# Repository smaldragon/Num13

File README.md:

# Num13

**Num13** is a 45-key compact ortholinear mechanical keyboard which includes a **Num**pad and is **13**Ux4U in size, which I designed for my own personal use.

The build is composed of 2 PCBs, the **top** pcb includes the key matrix (MX switches or low-profile Redragon switches w/ plate stabs), while the **bottom** includes the keyboard controller (a pi pico), a status led (rgb on the rB revision included here), and serves as the base of the keyboard structure itself.

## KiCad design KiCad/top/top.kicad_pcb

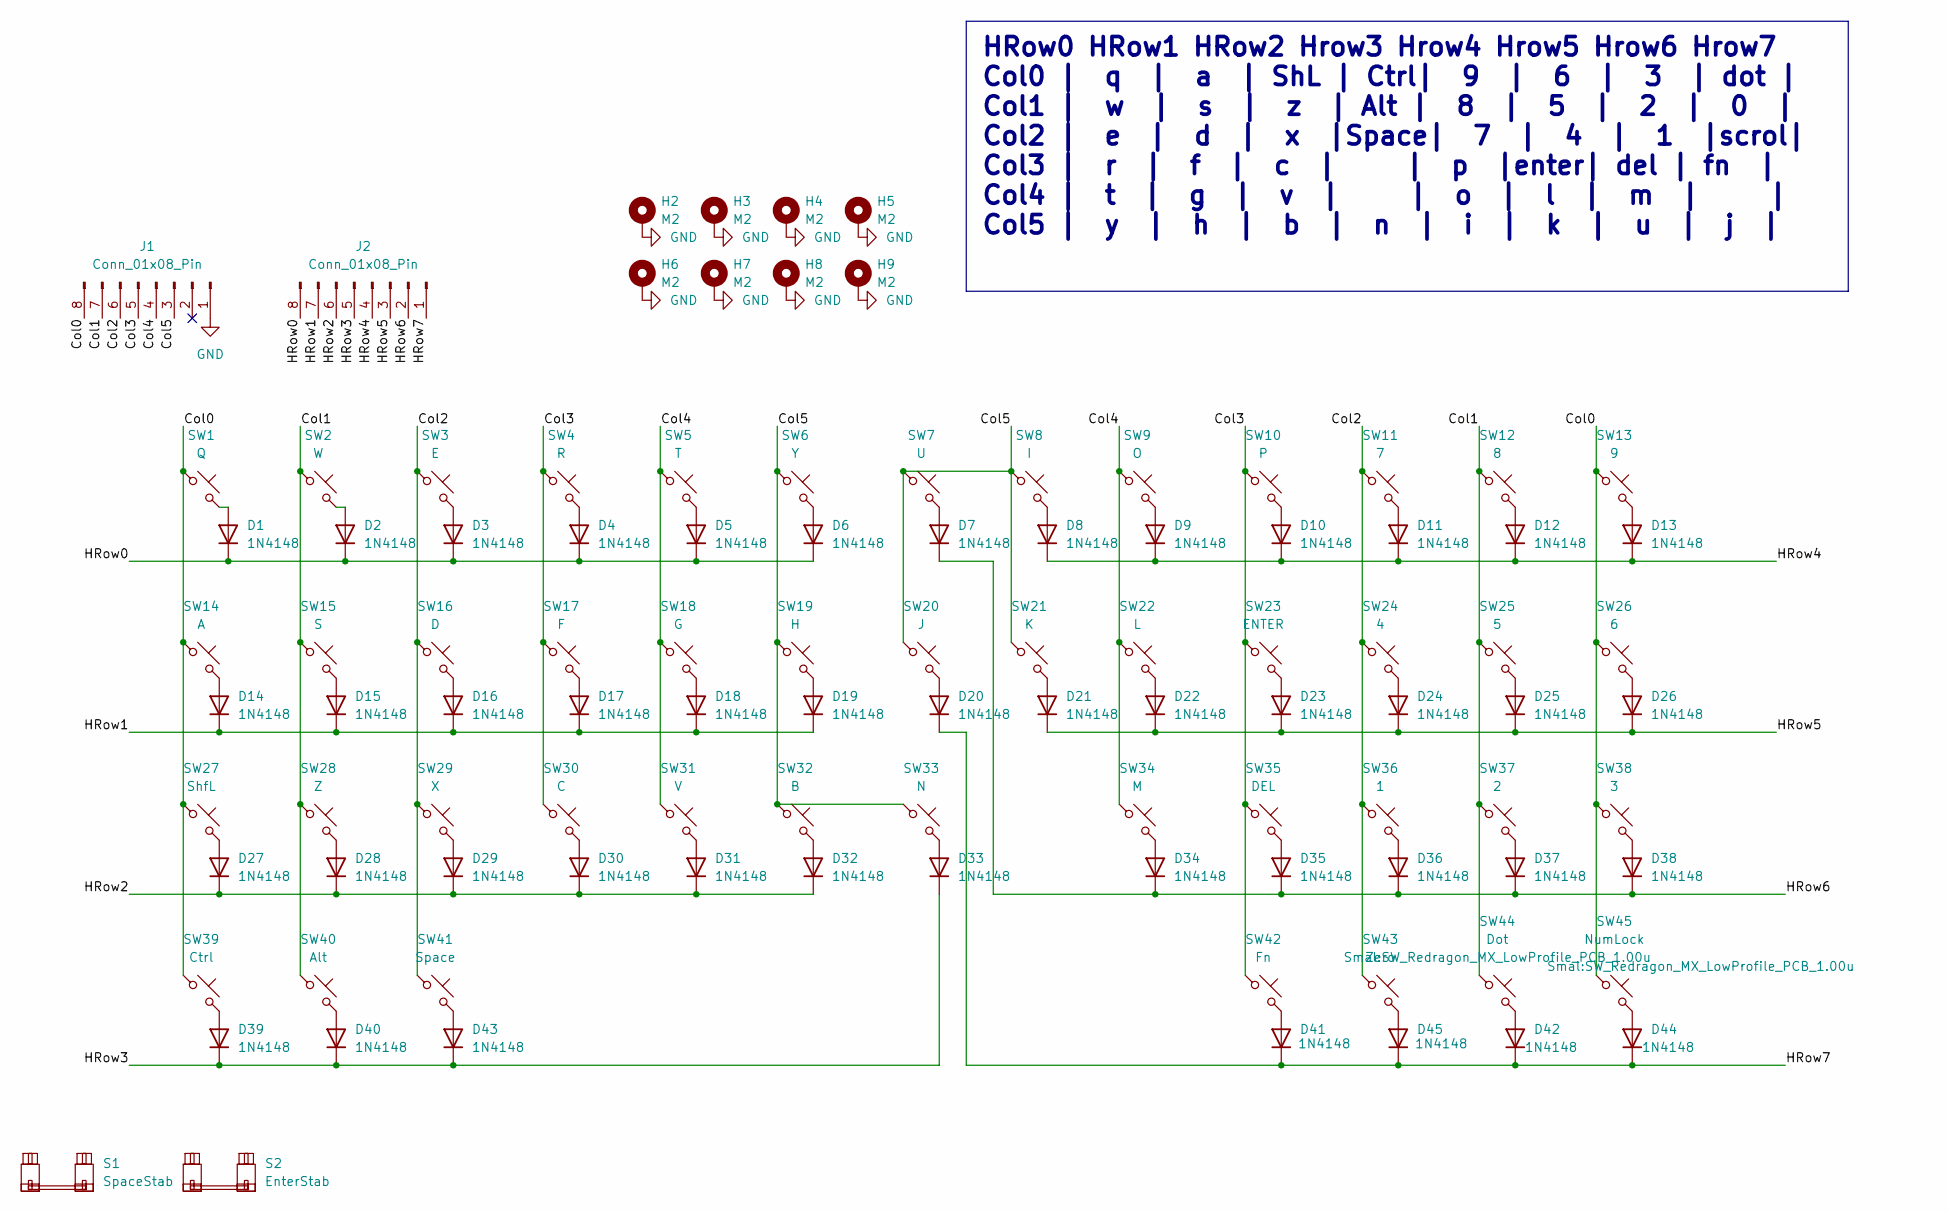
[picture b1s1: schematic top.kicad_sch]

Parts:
D1, D2, D3, D4, D5, D6, D7, D8, D9, D10, D11, D12, D13, D14, D15, D16, D17, D18, D19, D20, D21, D22, D23, D24, D25, D26, D27, D28, D29, D30, D31, D32, D33, D34, D35, D36, D37, D38, D39, D40, D41, D42, D43, D44, D45: 1N4148; D_DO-35_SOD27_P7.62mm_Horizontal
H2, H3, H4, H5, H6, H7, H8, H9: M2; MountingHole_2.2mm_M2_Pad
J1, J2: Conn_01x08_Pin; PinHeader_1x08_P2.54mm_Vertical
S1: SpaceStab; ks27_7u_pcb_cherry_plate
S2: EnterStab; ks27_2u_pcb_cherry_plate_stab
SW1: Q; SW_Redragon_MX_LowProfile_PCB_1.00u
SW2: W; SW_Redragon_MX_LowProfile_PCB_1.00u
SW3: E; SW_Redragon_MX_LowProfile_PCB_1.00u
SW4: R; SW_Redragon_MX_LowProfile_PCB_1.00u
SW5: T; SW_Redragon_MX_LowProfile_PCB_1.00u
SW6: Y; SW_Redragon_MX_LowProfile_PCB_1.00u
SW7: U; SW_Redragon_MX_LowProfile_PCB_1.00u
SW8: I; SW_Redragon_MX_LowProfile_PCB_1.00u
SW9: O; SW_Redragon_MX_LowProfile_PCB_1.00u
SW10: P; SW_Redragon_MX_LowProfile_PCB_1.00u
SW11: 7; SW_Redragon_MX_LowProfile_PCB_1.00u
SW12: 8; SW_Redragon_MX_LowProfile_PCB_1.00u
SW13: 9; SW_Redragon_MX_LowProfile_PCB_1.00u
SW14: A; SW_Redragon_MX_LowProfile_PCB_1.00u
SW15: S; SW_Redragon_MX_LowProfile_PCB_1.00u
SW16: D; SW_Redragon_MX_LowProfile_PCB_1.00u
SW17: F; SW_Redragon_MX_LowProfile_PCB_1.00u
SW18: G; SW_Redragon_MX_LowProfile_PCB_1.00u
SW19: H; SW_Redragon_MX_LowProfile_PCB_1.00u
SW20: J; SW_Redragon_MX_LowProfile_PCB_1.00u
SW21: K; SW_Redragon_MX_LowProfile_PCB_1.00u
SW22: L; SW_Redragon_MX_LowProfile_PCB_1.00u
SW23: ENTER; SW_Redragon_MX_LowProfile_PCB_2.00u
SW24: 4; SW_Redragon_MX_LowProfile_PCB_1.00u
SW25: 5; SW_Redragon_MX_LowProfile_PCB_1.00u
SW26: 6; SW_Redragon_MX_LowProfile_PCB_1.00u
SW27: ShfL; SW_Redragon_MX_LowProfile_PCB_1.00u
SW28: Z; SW_Redragon_MX_LowProfile_PCB_1.00u
SW29: X; SW_Redragon_MX_LowProfile_PCB_1.00u
SW30: C; SW_Redragon_MX_LowProfile_PCB_1.00u
SW31: V; SW_Redragon_MX_LowProfile_PCB_1.00u
SW32: B; SW_Redragon_MX_LowProfile_PCB_1.00u
SW33: N; SW_Redragon_MX_LowProfile_PCB_1.00u
SW34: M; SW_Redragon_MX_LowProfile_PCB_1.00u
SW35: DEL; SW_Redragon_MX_LowProfile_PCB_1.00u
SW36: 1; SW_Redragon_MX_LowProfile_PCB_1.00u
SW37: 2; SW_Redragon_MX_LowProfile_PCB_1.00u
SW38: 3; SW_Redragon_MX_LowProfile_PCB_1.00u
SW39: Ctrl; SW_Redragon_MX_LowProfile_PCB_1.00u
SW40: Alt; SW_Redragon_MX_LowProfile_PCB_1.00u
SW41: Space; SW_Redragon_MX_LowProfile_PCB_7.00u
SW42: Fn; SW_Redragon_MX_LowProfile_PCB_1.00u
SW43: Zero; SW_Redragon_MX_LowProfile_PCB_1.00u
SW44: Dot; SW_Redragon_MX_LowProfile_PCB_1.00u
SW45: NumLock; SW_Redragon_MX_LowProfile_PCB_1.00u

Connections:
/Col0: J1.8, SW1.1, SW13.1, SW14.1, SW26.1, SW27.1, SW38.1, SW39.1, SW45.1
/Col1: J1.7, SW2.1, SW12.1, SW15.1, SW25.1, SW28.1, SW37.1, SW40.1, SW44.1
/Col2: J1.6, SW3.1, SW11.1, SW16.1, SW24.1, SW29.1, SW36.1, SW41.1, SW43.1
/Col3: J1.5, SW4.1, SW10.1, SW17.1, SW23.1, SW30.1, SW35.1, SW42.1
/Col4: J1.4, SW5.1, SW9.1, SW18.1, SW22.1, SW31.1, SW34.1
/Col5: J1.3, SW6.1, SW7.1, SW8.1, SW19.1, SW20.1, SW21.1, SW32.1, SW33.1
/HRow0: D1.1 (K), D2.1 (K), D3.1 (K), D4.1 (K), D5.1 (K), D6.1 (K), J2.8
/HRow1: D14.1 (K), D15.1 (K), D16.1 (K), D17.1 (K), D18.1 (K), D19.1 (K), J2.7
/HRow2: D27.1 (K), D28.1 (K), D29.1 (K), D30.1 (K), D31.1 (K), D32.1 (K), J2.6
/HRow3: D33.1 (K), D39.1 (K), D40.1 (K), D43.1 (K), J2.5
/HRow4: D8.1 (K), D9.1 (K), D10.1 (K), D11.1 (K), D12.1 (K), D13.1 (K), J2.4
/HRow5: D21.1 (K), D22.1 (K), D23.1 (K), D24.1 (K), D25.1 (K), D26.1 (K), J2.3
/HRow6: D7.1 (K), D34.1 (K), D35.1 (K), D36.1 (K), D37.1 (K), D38.1 (K), J2.2
/HRow7: D20.1 (K), D41.1 (K), D42.1 (K), D44.1 (K), D45.1 (K), J2.1
GND: H2.1, H3.1, H4.1, H5.1, H6.1, H7.1, H8.1, H9.1, J1.1
unnamed: D1.2 (A), SW1.2
unnamed: D2.2 (A), SW2.2
unnamed: D3.2 (A), SW3.2
unnamed: D4.2 (A), SW4.2
unnamed: D5.2 (A), SW5.2
unnamed: D6.2 (A), SW6.2
unnamed: D7.2 (A), SW7.2
unnamed: D8.2 (A), SW8.2
unnamed: D9.2 (A), SW9.2
unnamed: D10.2 (A), SW10.2
unnamed: D11.2 (A), SW11.2
unnamed: D12.2 (A), SW12.2
unnamed: D13.2 (A), SW13.2
unnamed: D14.2 (A), SW14.2
unnamed: D15.2 (A), SW15.2
unnamed: D16.2 (A), SW16.2
unnamed: D17.2 (A), SW17.2
unnamed: D18.2 (A), SW18.2
unnamed: D19.2 (A), SW19.2
unnamed: D20.2 (A), SW20.2
unnamed: D21.2 (A), SW21.2
unnamed: D22.2 (A), SW22.2
unnamed: D23.2 (A), SW23.2
unnamed: D24.2 (A), SW24.2
unnamed: D25.2 (A), SW25.2
unnamed: D26.2 (A), SW26.2
unnamed: D27.2 (A), SW27.2
unnamed: D28.2 (A), SW28.2
unnamed: D29.2 (A), SW29.2
unnamed: D30.2 (A), SW30.2
unnamed: D31.2 (A), SW31.2
unnamed: D32.2 (A), SW32.2
unnamed: D33.2 (A), SW33.2
unnamed: D34.2 (A), SW34.2
unnamed: D35.2 (A), SW35.2
unnamed: D36.2 (A), SW36.2
unnamed: D37.2 (A), SW37.2
unnamed: D38.2 (A), SW38.2
unnamed: D39.2 (A), SW39.2
unnamed: D40.2 (A), SW40.2
unnamed: D41.2 (A), SW42.2
unnamed: D42.2 (A), SW44.2
unnamed: D43.2 (A), SW41.2
unnamed: D44.2 (A), SW45.2
unnamed: D45.2 (A), SW43.2

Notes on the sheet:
HRow0 HRow1 HRow2 Hrow3 Hrow4 Hrow5 Hrow6 Hrow7 Col0 | q | a | ShL | Ctrl| 9 | 6 | 3 | dot | Col1 | w | s | z | Alt | 8 | 5 | 2 | 0 | Col2 | e | d | x |Space| 7 | 4 | 1 |scrol| Col3 | r | f | c | | p |enter| del | fn | Col4 | t | g | v | | o | l | m | | Col5 | y | h | b | n | i | k | u | j |

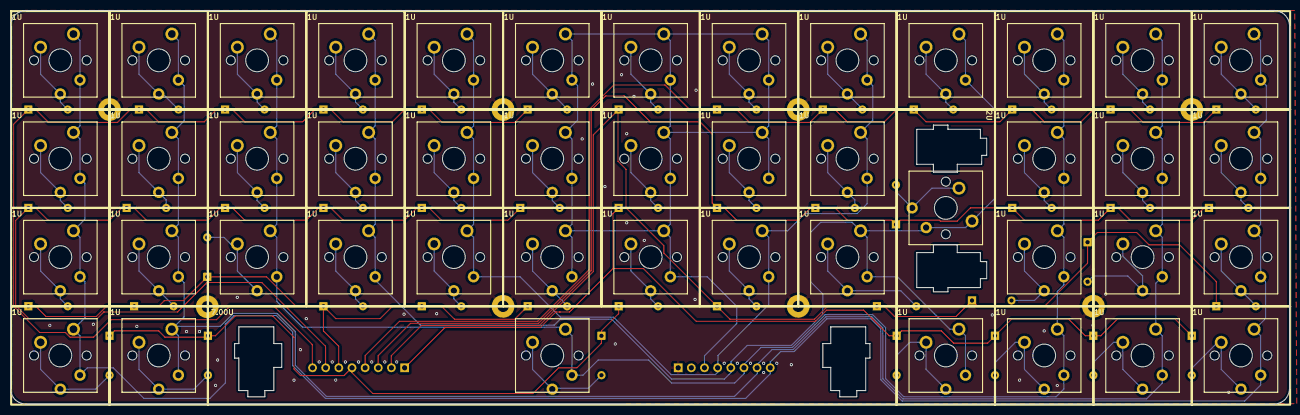
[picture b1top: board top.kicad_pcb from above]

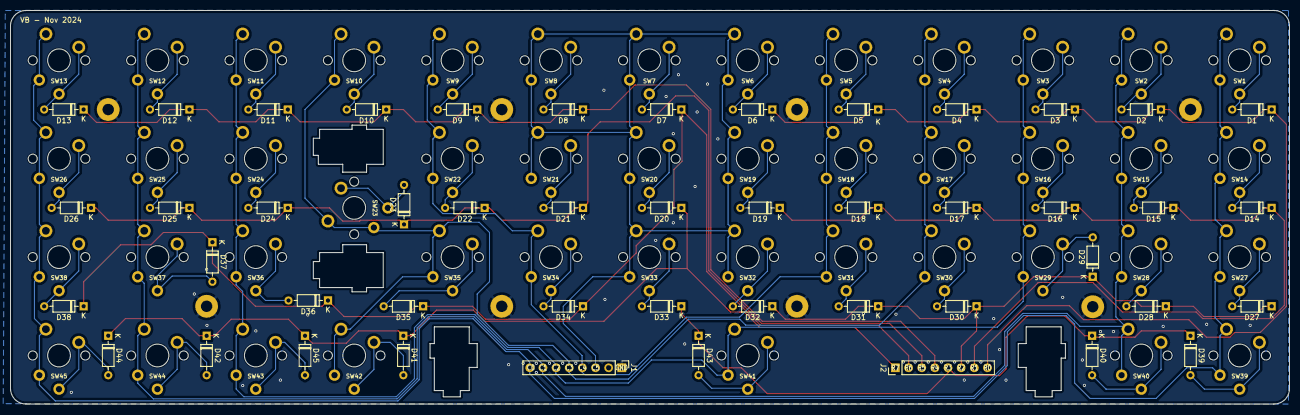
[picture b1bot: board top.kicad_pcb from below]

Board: 2 copper layers, 247.0 x 76.0 mm, 102 parts (47 on the bottom side), 60 nets.

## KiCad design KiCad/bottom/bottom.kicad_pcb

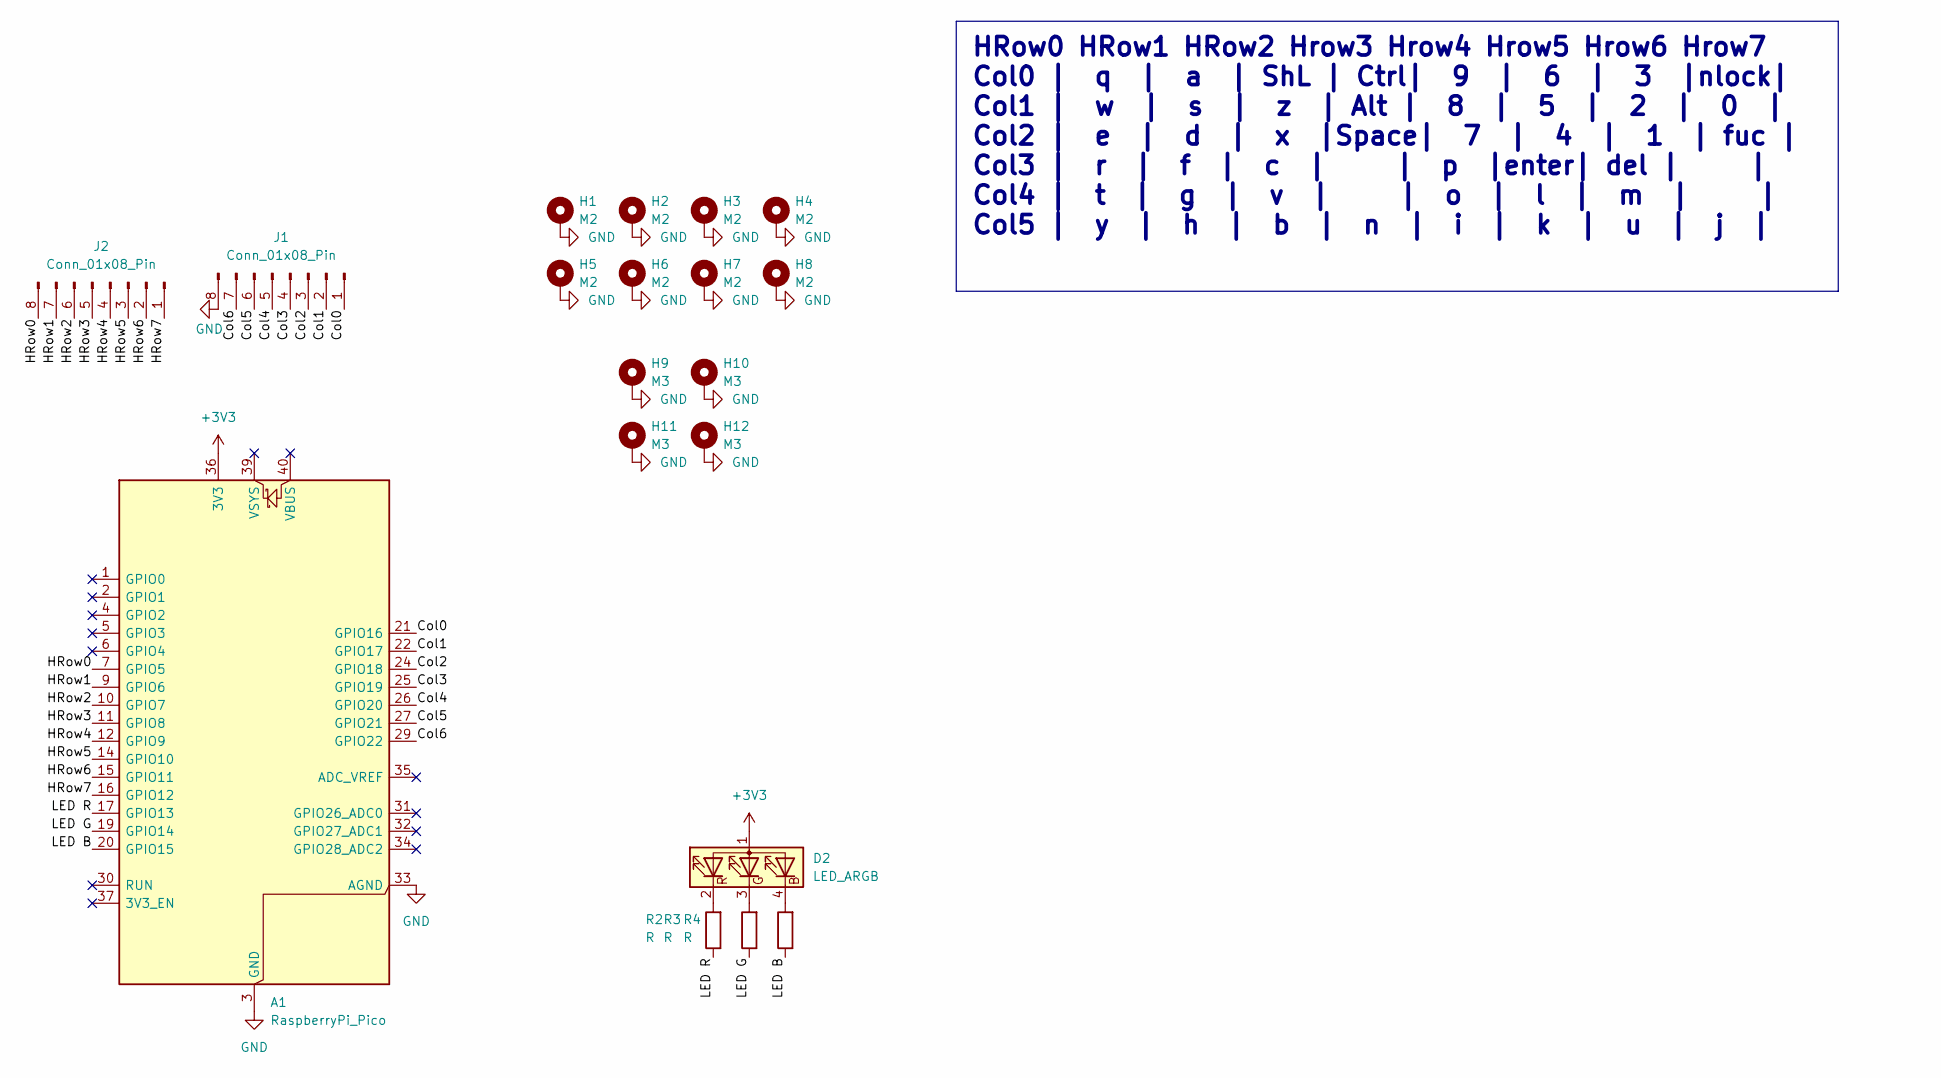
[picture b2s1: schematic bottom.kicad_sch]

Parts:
A1: RaspberryPi_Pico; RaspberryPi_Pico_Common_SMD
D2: LED_ARGB; ARGB horizontal
H1, H2, H3, H4, H5, H6, H7, H8: M2; MountingHole_2.2mm_M2_Pad
H9, H10, H11, H12: M3; MountingHole_3.2mm_M3_Pad
J1, J2: Conn_01x08_Pin; Harwin_M20-89008xx_1x08_P2.54mm_Horizontal
R2, R3, R4: R; R_0805_2012Metric

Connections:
+3V3: A1.36 (3V3), D2.1 (A)
/Col0: A1.21 (GPIO16), J1.1
/Col1: A1.22 (GPIO17), J1.2
/Col2: A1.24 (GPIO18), J1.3
/Col3: A1.25 (GPIO19), J1.4
/Col4: A1.26 (GPIO20), J1.5
/Col5: A1.27 (GPIO21), J1.6
/Col6: A1.29 (GPIO22), J1.7
/HRow0: A1.7 (GPIO5), J2.8
/HRow1: A1.9 (GPIO6), J2.7
/HRow2: A1.10 (GPIO7), J2.6
/HRow3: A1.11 (GPIO8), J2.5
/HRow4: A1.12 (GPIO9), J2.4
/HRow5: A1.14 (GPIO10), J2.3
/HRow6: A1.15 (GPIO11), J2.2
/HRow7: A1.16 (GPIO12), J2.1
/LED B: A1.20 (GPIO15), R4.1
/LED G: A1.19 (GPIO14), R3.1
/LED R: A1.17 (GPIO13), R2.1
GND: A1.3 (GND), A1.8 (GND), A1.13 (GND), A1.18 (GND), A1.23 (GND), A1.28 (GND), A1.33 (AGND), A1.38 (GND), H1.1, H2.1, H3.1, H4.1, H5.1, H6.1, H7.1, H8.1, H9.1, H10.1, H11.1, H12.1, J1.8
unnamed: D2.4 (BK), R4.2
unnamed: D2.3 (GK), R3.2
unnamed: D2.2 (RK), R2.2

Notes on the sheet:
HRow0 HRow1 HRow2 Hrow3 Hrow4 Hrow5 Hrow6 Hrow7 Col0 | q | a | ShL | Ctrl| 9 | 6 | 3 |nlock| Col1 | w | s | z | Alt | 8 | 5 | 2 | 0 | Col2 | e | d | x |Space| 7 | 4 | 1 | fuc | Col3 | r | f | c | | p |enter| del | | Col4 | t | g | v | | o | l | m | | Col5 | y | h | b | n | i | k | u | j |

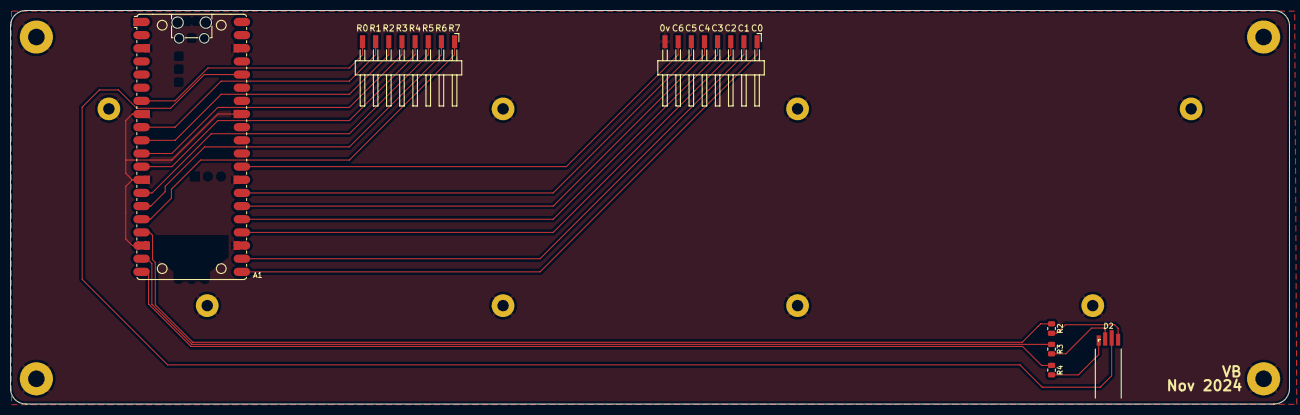
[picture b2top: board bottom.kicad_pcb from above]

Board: 2 copper layers, 247.0 x 76.0 mm, 19 parts (0 on the bottom side), 23 nets.

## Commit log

2024-10-29 add firmware files
2024-12-24 Add dvorak layout
